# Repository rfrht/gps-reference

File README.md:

# GPS-Referenced Programmable Precision Signal Generator

**Current state:** Project Stage. [Issues](https://github.com/rfrht/gps-reference/issues?q=is%3Aissue+is%3Aclosed)

**Next steps:** Procure, build, assemble, test.

## Overview

This is the do-it-yourself version of the u-Blox-based **GPS-Referenced Programmable Precision Signal Generator**.

In this version/revision, there's a Si5351-C clock generator driven by the GPS signal, hoping to be able to get more and cleaner signals using the GPS as a reference. See the [schematic](/gps-schematics.pdf).

There are two I²C ports - one from the the U-Blox and other for the Si5351C device. The clock signal level is TTL 3.3V.

The board was inspired by [ZL2PD design](https://www.zl2pd.com/GPS_Freq_Ref.html) and features a few other stuff, like break-out headers for I2C, Serial, USB, External Battery and antenna selector.

RA3APW [did some some extensive research (Russian content)](http://www.ra3apw.ru/proekty/ublox-neo-7m/) and found that there are a few frequencies where there is some very good precision for the general hobbyist, yielding precision between 0.1 PPM to 1 PPB. This is not a [GPS-Disciplined Oscillator](https://en.wikipedia.org/wiki/GPS_disciplined_oscillator) but a high precision [Numerically Controlled Oscillator](https://en.wikipedia.org/wiki/Numerically_controlled_oscillator) instead.

Bear in mind that the RA3APW tested U-Blox M-7 hardware, while in this project we will be using the newer generation [NEO-M8Q-01A Automotive grade](https://www.u-blox.com/en/product/neo-m8q-01a-module), which sports a [TCXO](https://en.wikipedia.org/wiki/Crystal_oscillator#Temperature), (hopefully) increasing precision.

## Configuration
Use the [U-Blox U-Center](https://www.u-blox.com/en/product/u-center) tool to configure your board. Open the Config page, in `TP5 (Timepulse 5)` menu and configure as per the below screenshot:

*U-Blox Configuration page - Click to enlarge*

### To do: document the 5351C setup

## Artefacts

The [schematics](/Schematics) are in Autodesk Eagle CAD format.

There is a [Gerber](/Design/gps-gerbers.zip) for ordering a PCB from your favourite PCB shop (Hint: $2 in jlcpcb.com for 5 units), as well a Digi-Key friendly [Bill of Materials](/Design/gps-bom.csv).

## Board pictures:
Board: (**Revision A, not this one**)

Cabled (with external wire antenna):

## TODO:
Check [Issues](https://github.com/rfrht/gps-reference/issues)

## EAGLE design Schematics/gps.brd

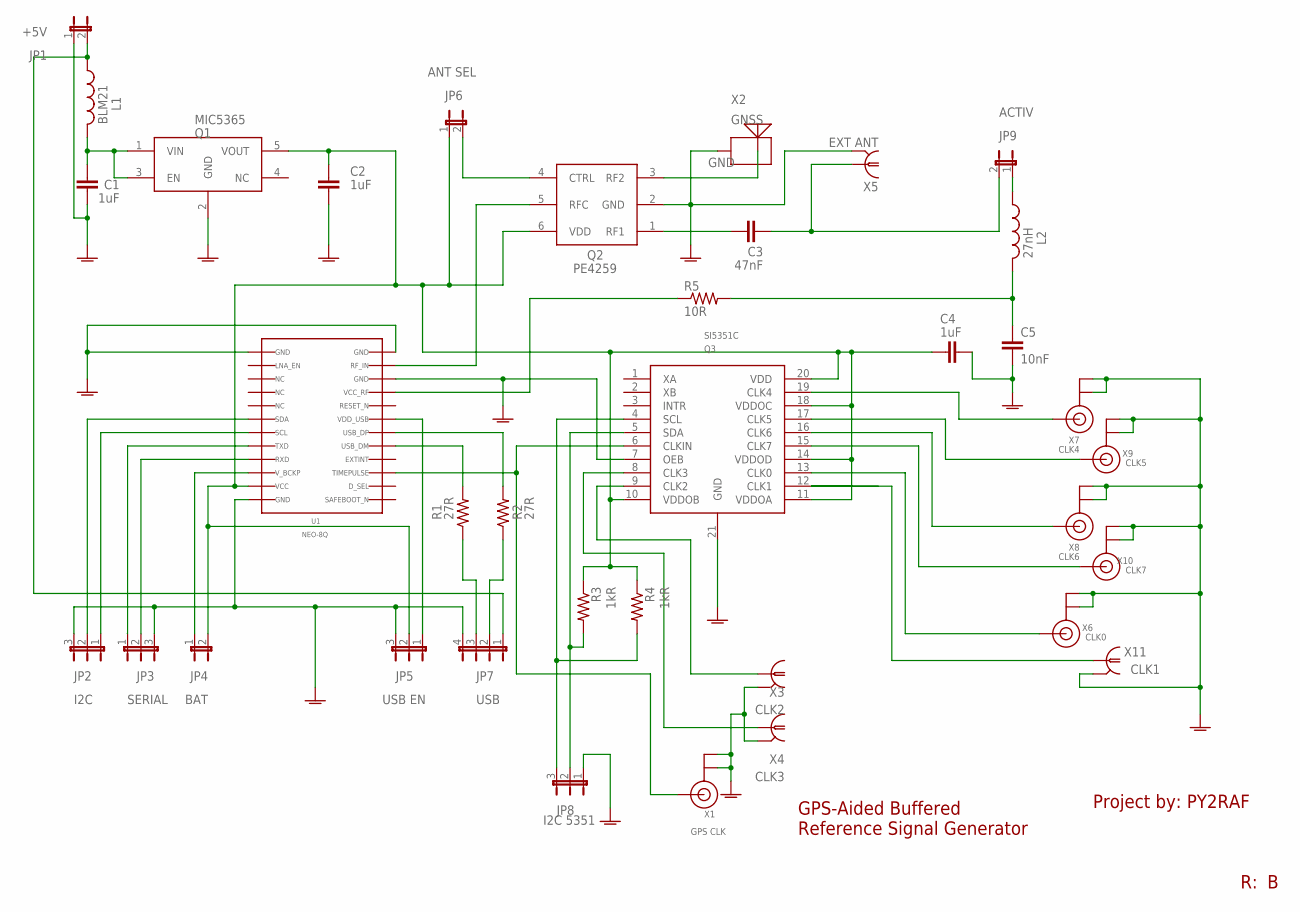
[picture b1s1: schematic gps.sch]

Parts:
C1, C2, C4: 1uF; C1206
C3: 47nF; C0805K
C5: 10nF; C0805K
JP1: +5V; JP1
JP2: I2C; JP2
JP3: SERIAL; JP2
JP4: BAT; JP1
JP5: USB EN; JP2
JP6: ANT SEL; JP1
JP7: USB; JP4
JP8: I2C 5351; JP2
JP9: ACTIV; JP1
L1: BLM21; L2012C
L2: 27nH; 0603
Q1: MIC5365; SOT23-5L
Q2: PE4259; SC-70
Q3: SI5351C; QFN20
R1, R2: 27R; M1206
R3, R4: 1kR; R1206
R5: 10R; R0805
U1: NEO-8Q; NEO-7
X1: GPS CLK; U.FL
X2: GNSS; MOLEX-GNSS
X3: CLK2; SMA-RF
X4: CLK3; SMA-RF
X5: EXT ANT; SMA-RF
X6: CLK0; U.FL
X7: CLK4; U.FL
X8: CLK6; U.FL
X9: CLK5; U.FL
X10: CLK7; U.FL
X11: CLK1; SMA-RF

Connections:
GNDA: C1.2, C2.2, C4.2, C5.2, JP1.1, JP2.3, JP3.3, JP5.3, JP7.4, JP8.1, Q1.2 (GND), Q2.2 (GND), Q3.7 (OEB), Q3.21 (GND), U1.10, U1.12, U1.13, U1.24, X1.1 (GND), X1.2 (GND), X2.P$1 (GRD), X2.P$3 (GRD), X2.P$4 (GRD), X3.2, X3.3 (2), X3.4 (2), X3.5 (2), X4.2, X4.3 (2), X4.4 (2), X4.5 (2), X5.2, X5.3 (2), X5.4 (2), X5.5 (2), X6.1 (GND), X6.2 (GND), X7.1 (GND), X7.2 (GND), X8.1 (GND), X8.2 (GND), X9.1 (GND), X9.2 (GND), X10.1 (GND), X10.2 (GND), X11.2, X11.3 (2), X11.4 (2), X11.5 (2)
unnamed: Q3.6 (CLKIN), U1.3, X1.3 (SIGNAL)
unnamed: Q3.12 (CLK1), X11.1
unnamed: Q3.9 (CLK2), X3.1
unnamed: JP8.3, Q3.4 (SCL), R4.2
unnamed: C3.2, JP9.2, X5.1
unnamed: C3.1, Q2.1 (RF1)
unnamed: R5.1, U1.9
unnamed: C5.1, L2.2, R5.2
unnamed: R1.2, U1.5
unnamed: R2.2, U1.6
unnamed: JP9.1, L2.1
unnamed: JP5.1, U1.7
unnamed: JP7.3, R1.1
unnamed: JP7.2, R2.1
unnamed: JP2.2, U1.18
unnamed: JP2.1, U1.19
unnamed: JP3.2, U1.21
unnamed: JP3.1, U1.20
unnamed: JP4.1, U1.22
unnamed: JP6.2, Q2.4 (CTRL)
unnamed: Q3.19 (CLK4), X7.3 (SIGNAL)
unnamed: C2.1, C4.1, JP4.2, JP5.2, JP6.1, Q1.5 (VOUT), Q2.6 (VDD), Q3.10 (VDDOB), Q3.11 (VDDOA), Q3.14 (VDDOD), Q3.18 (VDDOC), Q3.20 (VDD), R3.1, R4.1, U1.23
unnamed: Q2.5 (RFC), U1.11
unnamed: C1.1, L1.2, Q1.1 (VIN), Q1.3 (EN)
unnamed: Q3.17 (CLK5), X9.3 (SIGNAL)
unnamed: Q2.3 (RF2), X2.P$2 (ANT)
unnamed: Q3.16 (CLK6), X8.3 (SIGNAL)
unnamed: JP1.2, JP7.1, L1.1
unnamed: Q3.15 (CLK7), X10.3 (SIGNAL)
unnamed: Q3.13 (CLK0), X6.3 (SIGNAL)
unnamed: Q3.8 (CLK3), X4.1
unnamed: JP8.2, Q3.5 (SDA), R3.2

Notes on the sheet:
GPS-Aided Buffered Reference Signal Generator
Project by:

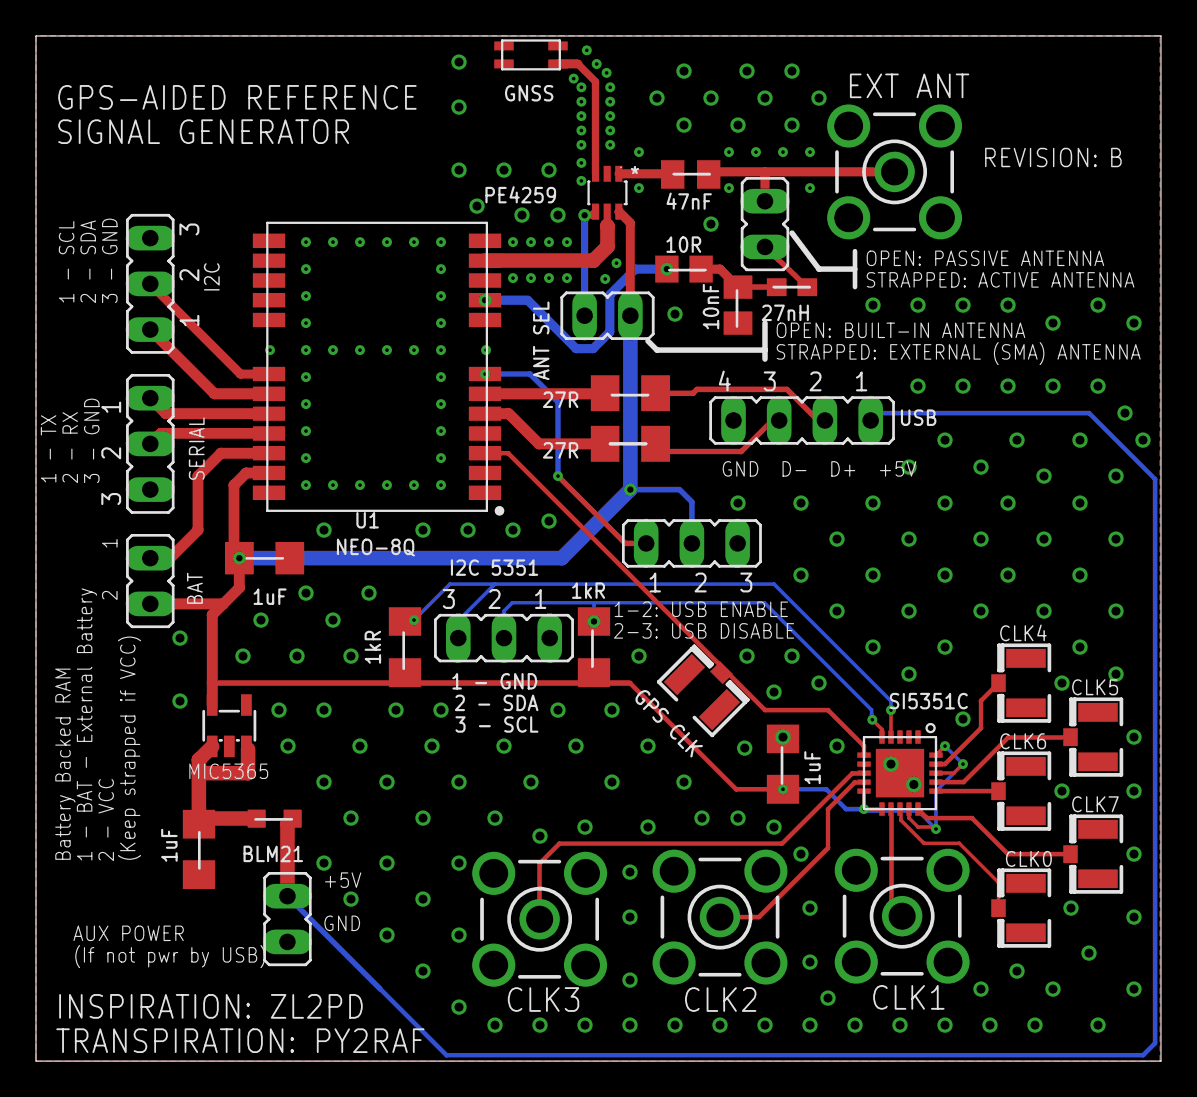
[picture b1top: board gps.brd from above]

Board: 2 copper layers, 62.5 x 57.0 mm, 36 parts (0 on the bottom side), 33 nets.

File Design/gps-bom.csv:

Qty,Value,Parts,Digi-Key PN
3,1uF,"C1, C2, C4",732-7685-1-ND
1,0.47uF,C3,399-14612-1-ND
1,1000pF,C5,399-1159-1-ND
1,JUMPER HDR,JP{1..9},PREC040SAAN-RC
1,BLM21,L1,490-1041-1-ND
1,27nH,L2,1276-6311-1-ND
1,MIC5365,Q1,576-4085-1-ND
1,PE4259,Q2,1046-1011-1-ND
1,SI5351C,Q3,336-5160-1-ND
2,27R,"R1, R2",RHM27CJCT-ND
2,1kR,"R3, R4",541-1.0KECT-ND
1,10R,R5,541-10ECT-ND
1,NEO-8Q,U1,672-1174-1-ND
4,SMA CONN,"X3, X4, X5, X11",A97594-ND
6,U.FL CONN,"X1, X2, X6, X7, X8, X9, X10",A118077CT-ND

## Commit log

2019-06-29 Revision A
    Initial commit
2019-06-29 Readme Rename
2019-06-29 A few corrections in Readme
2019-06-30 A few README enhancement
2019-07-01 A few more fluff in Readme
2019-07-01 Moar Readme changes
2019-07-02 A few README changes
2019-07-02 A few more readme updates
2019-07-03 Straightened a Serial port Route
2019-07-03 Status update
2019-08-31 Updated Readme with test data
2019-08-31 Fixed URLs in readme
2019-10-30 Fixed URL - Pointing to rf3.org
2019-12-09 New GPS version: Now feeding a Si5351
    Test version.
2019-12-10 Rev. B: Pull-up in I2C, new GPS Clock port
    * Implemented I²C pull-up resistors (required by datasheet)
    * Added a U.FL connector in the GPS clock port that drives the 5351 in
    for test / troubleshoot
    * Added schematic, gerber, pictures
2019-12-10 GPS board: I2C changes
    * Separated to two independent I2C ports, one for the uBlox, other for
    the 5351
    * Minor re-routing
    * Updated BOM, schematics and stuff
2019-12-10 Sync-up
